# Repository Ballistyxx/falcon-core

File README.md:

# Falcon Core

<!-- <table>
  <tr>
    <td></td>
    <td></td>
  </tr>
</table> -->

A custom standalone ESP32-S3 flight controller for an indoor autonomous blimp. Successor to [Falcon Flight](https://github.com/PHS-SMCS/falcon-flight), redesigned from a Raspberry Pi Zero 2W HAT into a purpose-built 32×46mm 4-layer PCB.

Sponsored by [PCBWay](https://www.pcbway.com/).

## Specifications

- **MCU:** ESP32-S3-WROOM-1 (N8R8/N16R8) — dual-core LX7, Wi-Fi, BLE, 8MB PSRAM
- **Camera:** OV2640 via 24-pin 0.5mm FFC, 8-bit DVP interface
- **IMU:** BMI270 (6-axis accel/gyro, I2C)
- **Magnetometer:** MMC5633NJL (3-axis AMR, I2C, 1.62–3.6V)
- **ToF Sensor:** VL53L5CX (I2C)
- **Motor Drivers:** 4× DRV8212P bidirectional H-bridge
- **Battery Sensing:** Internal ADC (GPIO7)
- **Status LED:** Programmable red LED (GPIO48)
- **Board:** 32×46mm, 4-layer, matte black solder mask
- **Weight:** only 11 grams (excluding battery)

## Power

- **Battery:** BetaFPV 3.7V 300mAh 1S LiPo
- **Charging:** TP4057 via USB-C (5.1kΩ CC pull-downs)
- **Motor Power:** Direct battery feed to DRV8212P VM pins
- **Logic Isolation:** BLM18PG221SN1D ferrite bead between battery and logic rail
- **Regulators (ME6211 LDOs, SOT-23-5):**
  - 3.3V — ESP32-S3, sensors, VDDIO
  - 2.8V × 2 — OV2640 AVDD and DOVDD
  - 1.2V — OV2640 DVDD

## GPIO Assignment

| GPIO | Function |
|------|----------|
| 1, 2 | SCCB (camera I2C — SIOD, SIOC) |
| 3 | M2_IN1 |
| 4 | M3_IN2 |
| 5 | M3_IN1 |
| 6 | M1_IN2 |
| 7 | BAT_ADC (battery voltage sensing) |
| 8, 18 | Main I2C bus (SDA, SCL) |
| 9, 10, 11, 12, 13, 14, 21, 40 | OV2640 DVP data bus (D8, D7, D6, D2, D5, D3, D4, D9) |
| 15 | M4_IN1 |
| 16 | M4_IN2 |
| 17 | M2_IN2 |
| 19, 20 | USB D−/D+ |
| 38 | Camera PCLK |
| 39 | Camera XCLK |
| 41 | HREF |
| 42 | VSYNC |
| 43, 44 | UART0 debug |
| 47 | M1_IN1 |
| 48 | Red LED (1kΩ to GND) |

Camera PWDN tied to GND, RESETB tied to 3.3V.

## I2C Bus

All sensors share the main I2C bus (GPIO8/18):

- BMI270 (accel/gyro)
- MMC5633NJL (magnetometer)
- VL53L5CX (time-of-flight)

Camera SCCB runs on a separate bus (GPIO1/2).

## Motor Layout

- 2× horizontal forward-facing motors (thrust)
- 1× downward-facing altitude motor (mounted below PCB on standoff)
- 1× TBD

## Firmware

Built with ESP-IDF. Custom PID stabilization (no ArduPilot). Communicates with a laptop over WebSocket for optical flow and AprilTag detection via OpenCV.

## License

See [LICENSE](LICENSE).

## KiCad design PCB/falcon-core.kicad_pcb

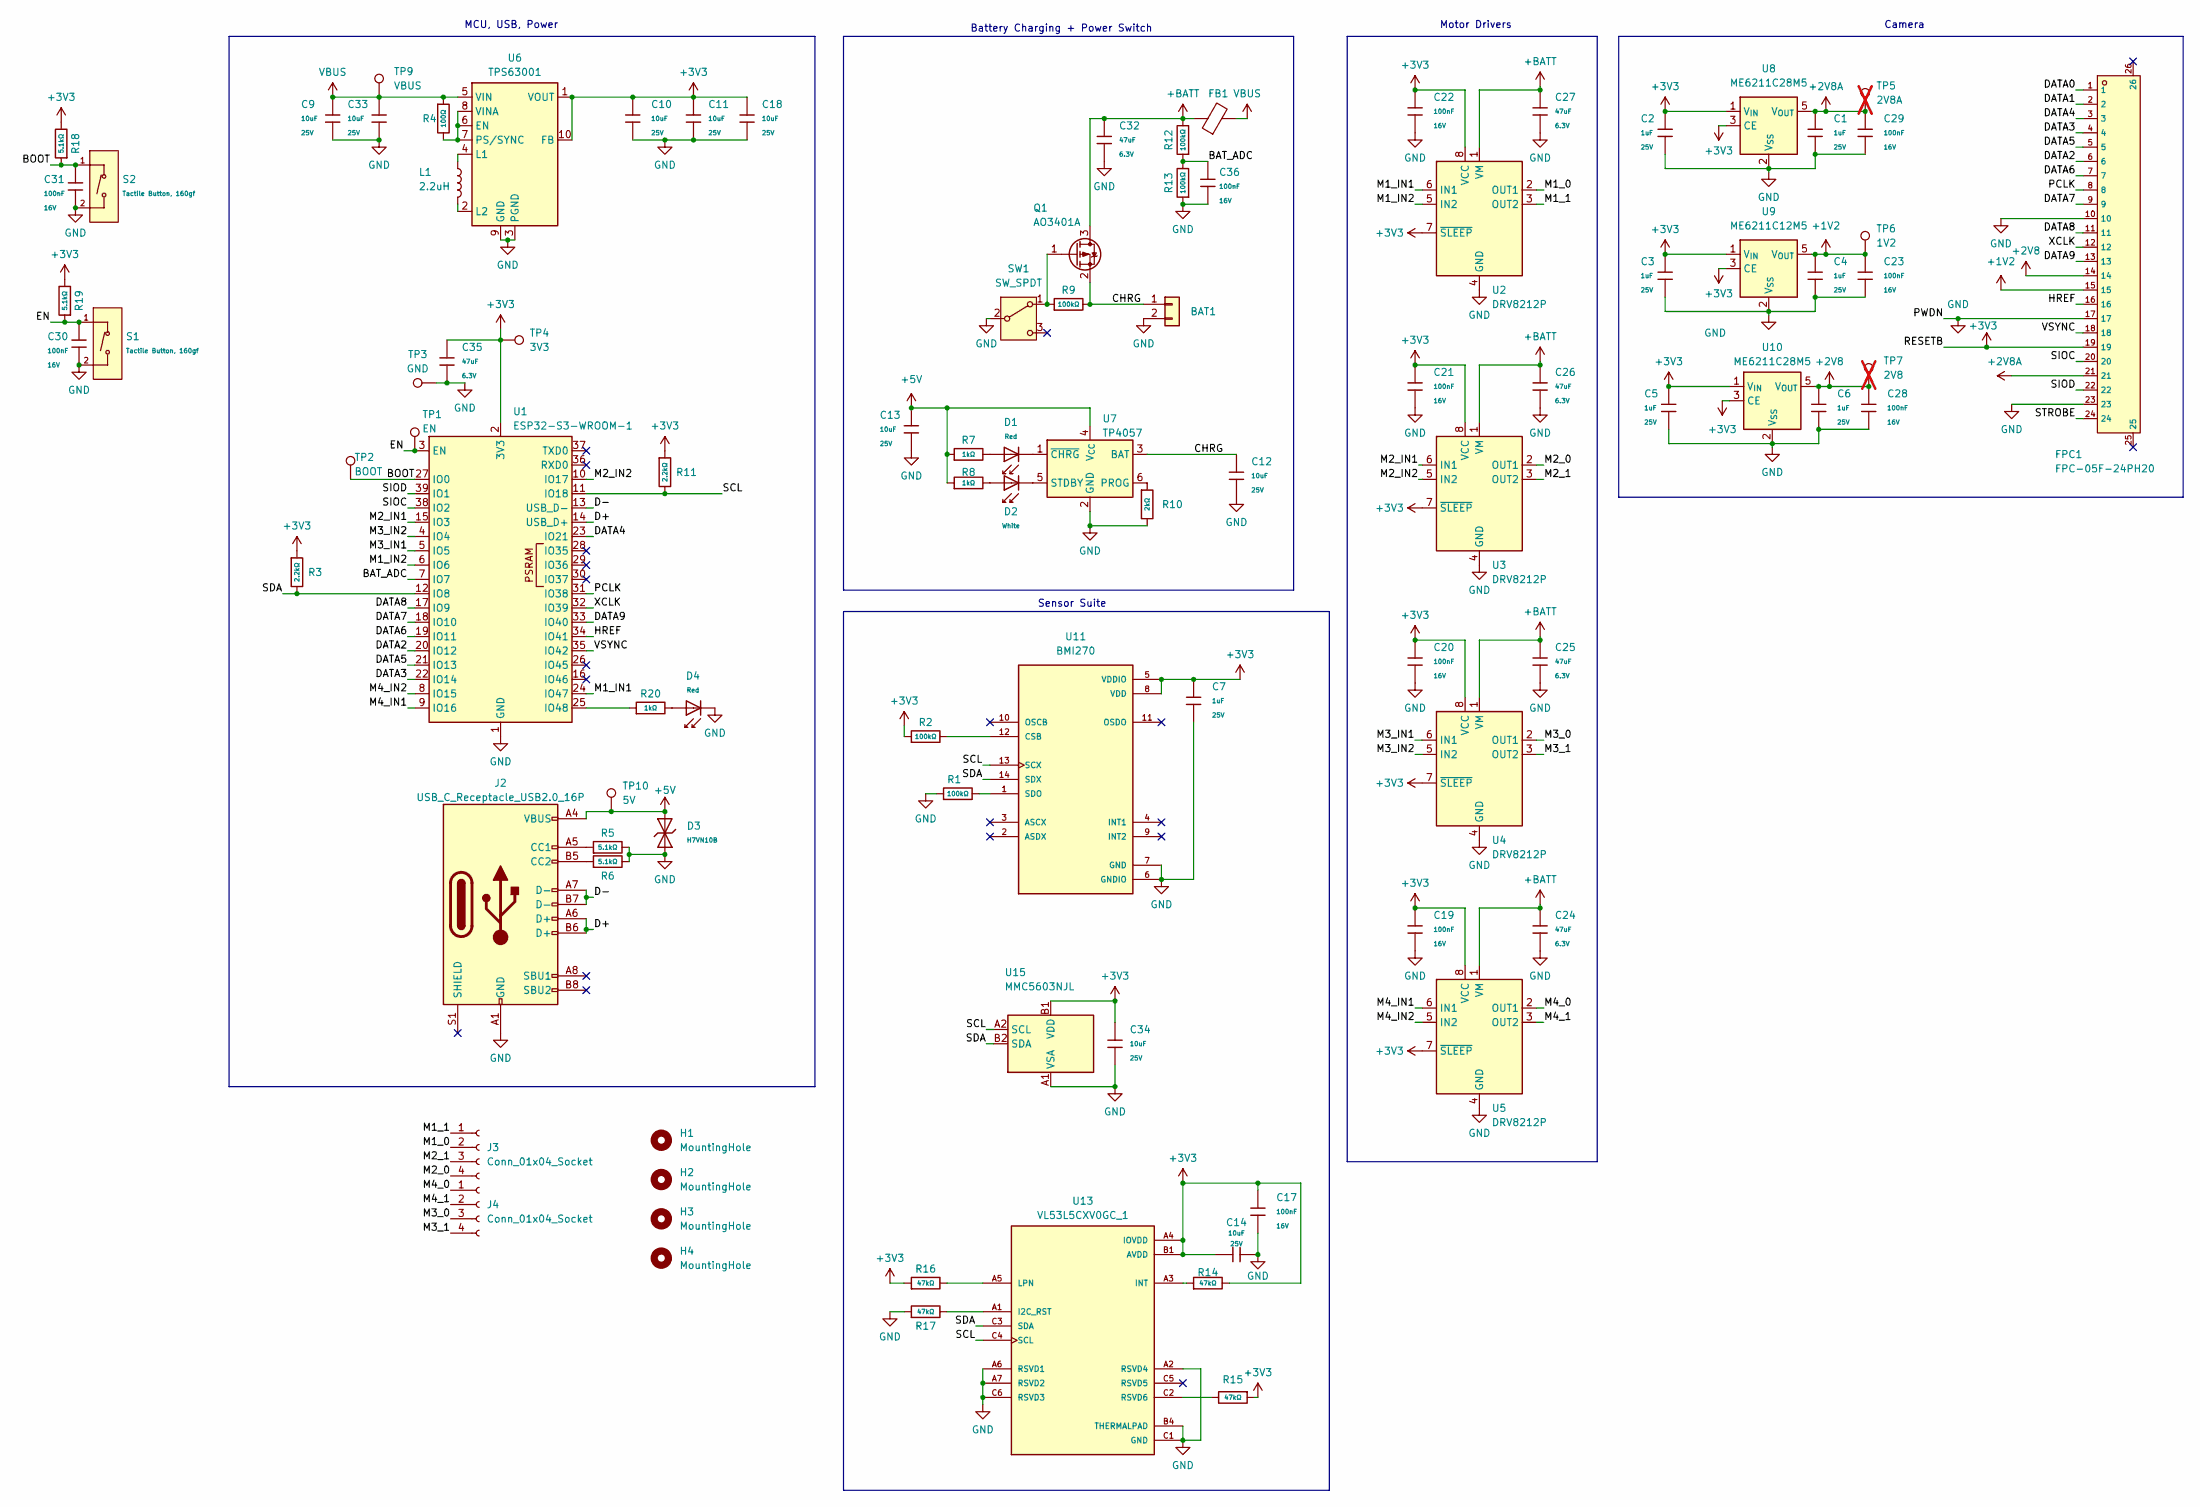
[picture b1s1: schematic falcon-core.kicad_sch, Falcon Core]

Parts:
BAT1: Conn_01x02; CONN-SMD_2P-P2.00_WF-1F200A2P; LCSC C23397052
C1, C2, C3, C4, C5, C6, C7: 1uF; C_0402; Voltage Rated 25V; Tolerance ±10%; Part CL05A105KA5NQNC; LCSC C52923
C9, C10, C11, C12, C13, C14, C18, C33, C34: 10uF; C_0603; Voltage Rated 25V; Tolerance ±20%; Part CL10A106MA8NRNC; LCSC C96446
C17, C19, C20, C21, C22, C23, C28, C29, C30, C31, C36: 100nF; C_0402; Voltage Rated 16V; Tolerance ±10%; Part CL05B104KO5NNNC; LCSC C1525
C24, C25, C26, C27, C32, C35: 47uF; C_0805; Voltage Rated 6.3V; Tolerance ±20%; Part CL21A476MQYNNNE; LCSC C16780
D1, D4: Red; D_0603; Part KT-0603R; LCSC C2286
D2: White; D_0603; Part KT-0603W; LCSC C2290
D3: H7VN10B; D_DFN1006-2L; Part H7VN10B; LCSC C20615788
FB1: FerriteBead; L_0603_1608Metric; LCSC Part Number C80165
FPC1: FPC-05F-24PH20; FPC-SMD_24P-P0.50_FPC-05F-24PH20; LCSC C2856805
H1, H2, H3, H4: MountingHole; MountingHole_3.2mm_M3_DIN965_Pad
J2: USB_C_Receptacle_USB2.0_16P; USB_C_Receptacle_GCT_USB4105-xx-A_16P_TopMnt_Horizontal; LCSC C393939
J3, J4: Conn_01x04_Socket; CONN-SMD_4P-P2.54_HX-PM2.54-1X4PWT; LCSC C46061768
L1: 2.2uH; L_APV_ANR252010; LCSC C5349606
Q1: AO3401A; SOT-23; LCSC C15127
R1, R2, R9, R12, R13: 100kΩ; R_0402; Overload Voltage (Max) 50V; Tolerance ±1%; Part 0402WGF1003TCE; LCSC C25741
R3, R11: 2.2kΩ; R_0402; Overload Voltage (Max) 50V; Tolerance ±1%; Part 0402WGF2201TCE; LCSC C25879
R4: 100Ω; R_0402; Overload Voltage (Max) 50V; Tolerance ±1%; Part 0402WGF1000TCE; LCSC C25076
R5, R6, R18, R19: 5.1kΩ; R_0402; Overload Voltage (Max) 50V; Tolerance ±1%; Part 0402WGF5101TCE; LCSC C25905
R7, R8, R20: 1kΩ; R_0402; Overload Voltage (Max) 50V; Tolerance ±1%; Part 0402WGF1001TCE; LCSC C11702
R10: 2kΩ; R_0402; Overload Voltage (Max) 50V; Tolerance ±1%; Part 0402WGF2001TCE; LCSC C4109
R14, R15, R16, R17: 47kΩ; R_0402; Overload Voltage (Max) 50V; Tolerance ±1%; Part 0402WGF4702TCE; LCSC C25792
S1, S2: Tactile Button, 160gf; SW_TS-1088-AR02016; Voltage Rating (Dc) 12V; Part TS-1088-AR02016; LCSC C720477
SW1: SW_SPDT; SW_Slide_SPDT_Angled_CK_OS102011MA1Q; LCSC C431547
TP1: EN; TestPoint_Pad_D2.0mm
TP2: BOOT; TestPoint_Pad_D2.0mm
TP3: GND; TestPoint_Pad_D2.0mm
TP4: 3V3; TestPoint_Pad_D2.0mm
TP5: 2V8A; TestPoint_Pad_D2.0mm; not fitted
TP6: 1V2; TestPoint_Pad_D2.0mm
TP7: 2V8; TestPoint_Pad_D2.0mm; not fitted
TP9: VBUS; TestPoint_Pad_D2.0mm
TP10: 5V; TestPoint_Pad_D2.0mm
U1: ESP32-S3-WROOM-1; LCSC C2913202
U2, U3, U4, U5: DRV8212P; WSON-8-1EP_2x2mm_P0.5mm_EP0.9x1.6mm_ThermalVias; LCSC C5208051
U6: TPS63001; Texas_DRC0010J_ThermalVias; LCSC C28060
U7: TP4057; TSOT-23-6; LCSC C12044
U8, U10: ME6211C28M5; SOT-23-5; LCSC C53099
U9: ME6211C12M5; SOT-23-5; LCSC C236672
U11: BMI270; XDCR_BMI270; LCSC C2836813
U13: VL53L5CXV0GC_1; XDCR_VL53L5CXV0GC_1; PARTREV 13; LCSC C3178303
U15: MMC5603NJL; WLP-4_0.86x0.86mm_P0.4mm; LCSC C404328

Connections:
+1V2: C4.1, C23.2, FPC1.15, TP6.1 (1_1), U9.5 (V_{OUT})
+2V8: C6.1, C28.2, FPC1.14, TP7.1, U10.5 (V_{OUT})
+2V8A: C1.1, C29.2, FPC1.21, TP5.1, U8.5 (V_{OUT})
+5V: C13.1, D3.2, J2.A4 (VBUS), J2.A9 (VBUS), J2.B4 (VBUS), J2.B9 (VBUS), R7.1, R8.1, TP10.1 (1_1), U7.4 (V_{CC})
+BATT: C24.1, C25.1, C26.1, C27.1, C32.1, FB1.1, Q1.3 (D), R12.2, U2.1 (VM), U3.1 (VM), U4.1 (VM), U5.1 (VM)
/BAT_ADC: C36.1, R12.1, R13.2, U1.7 (IO7)
/BOOT: C31.1, R18.1, S2.1 (A), TP2.1 (1_1), U1.27 (IO0)
/CHRG: BAT1.1, C12.1, Q1.2 (S), R9.2, U7.3 (BAT)
/D+: J2.A6 (D+), J2.B6 (D+), U1.14 (USB_D+)
/D-: J2.A7 (D-), J2.B7 (D-), U1.13 (USB_D-)
/DATA0: FPC1.1
/DATA1: FPC1.2
/DATA2: FPC1.6, U1.20 (IO12)
/DATA3: FPC1.4, U1.22 (IO14)
/DATA4: FPC1.3, U1.23 (IO21)
/DATA5: FPC1.5, U1.21 (IO13)
/DATA6: FPC1.7, U1.19 (IO11)
/DATA7: FPC1.9, U1.18 (IO10)
/DATA8: FPC1.11, U1.17 (IO9)
/DATA9: FPC1.13, U1.33 (IO40)
/HREF: FPC1.16, U1.34 (IO41)
/M1_0: J3.2, U2.2 (OUT1)
/M1_1: J3.1, U2.3 (OUT2)
/M1_IN1: U1.24 (IO47), U2.6 (IN1)
/M1_IN2: U1.6 (IO6), U2.5 (IN2)
/M2_0: J3.4, U3.2 (OUT1)
/M2_1: J3.3, U3.3 (OUT2)
/M2_IN1: U1.15 (IO3), U3.6 (IN1)
/M2_IN2: U1.10 (IO17), U3.5 (IN2)
/M3_0: J4.3, U4.2 (OUT1)
/M3_1: J4.4, U4.3 (OUT2)
/M3_IN1: U1.5 (IO5), U4.6 (IN1)
/M3_IN2: U1.4 (IO4), U4.5 (IN2)
/M4_0: J4.1, U5.2 (OUT1)
/M4_1: J4.2, U5.3 (OUT2)
/M4_IN1: U1.9 (IO16), U5.6 (IN1)
/M4_IN2: U1.8 (IO15), U5.5 (IN2)
/PCLK: FPC1.8, U1.31 (IO38)
/SCL: R11.2, U1.11 (IO18), U11.13 (SCX), U13.C4 (SCL), U15.A2 (SCL)
/SDA: R3.2, U1.12 (IO8), U11.14 (SDX), U13.C3 (SDA), U15.B2 (SDA)
/SIOC: FPC1.20, U1.38 (IO2)
/SIOD: FPC1.22, U1.39 (IO1)
/STROBE: FPC1.24
/VSYNC: FPC1.18, U1.35 (IO42)
/XCLK: FPC1.12, U1.32 (IO39)
GND: BAT1.2, C1.2, C2.2, C3.2, C4.2, C5.2, C6.2, C7.2, C9.2, C10.2, C11.2, C12.2, C13.2, C14.2, C17.2, C18.2, C19.1, C20.1, C21.1, C22.1, C23.1, C24.2, C25.2, C26.2, C27.2, C28.1, C29.1, C30.2, C31.2, C32.2, C33.2, C34.1, C35.2, C36.2, D3.1, D4.1, FPC1.10, FPC1.17, FPC1.23, J2.A1 (GND), J2.A12 (GND), J2.B1 (GND), J2.B12 (GND), R1.1, R5.2, R6.2, R10.2, R13.1, R17.1, S1.2 (B), S2.2 (B), SW1.2 (B), TP3.1 (1_1), U1.1 (GND), U1.40 (GND), U1.41 (GND), U2.4 (GND), U2.9 (GND), U3.4 (GND), U3.9 (GND), U4.4 (GND), U4.9 (GND), U5.4 (GND), U5.9 (GND), U6.3 (PGND), U6.9 (GND), U6.11 (PGND), U7.2 (GND), U8.2 (V_{SS}), U9.2 (V_{SS}), U10.2 (V_{SS}), U11.6 (GNDIO), U11.7 (GND), U13.A2 (RSVD4), U13.A6 (RSVD1), U13.A7 (RSVD2), U13.B4 (THERMALPAD), U13.C1 (GND), U13.C6 (RSVD3), U13.C7 (GND), U15.A1 (VSA); also elsewhere on the board
unnamed: D1.2, R7.2
unnamed: D2.2, R8.2
unnamed: D4.2, R20.2
unnamed: J2.A5 (CC1), R5.1
unnamed: J2.B5 (CC2), R6.1
unnamed: Q1.1 (G), R9.1, SW1.1 (A)
unnamed: R20.1, U1.25 (IO48)
unnamed: R4.2, U6.6 (EN), U6.7 (PS/SYNC), U6.8 (VINA)
unnamed: L1.1, U6.4 (L1)
unnamed: L1.2, U6.2 (L2)
unnamed: R10.1, U7.6 (PROG)
unnamed: D2.1, U7.5 (STDBY)
unnamed: D1.1, U7.1 (~CHRG)
unnamed: R2.2, U11.12 (CSB)
unnamed: R1.2, U11.1 (SDO)
unnamed: R17.2, U13.A1 (I2C_RST)
unnamed: R14.1, U13.A3 (INT)
unnamed: R16.2, U13.A5 (LPN)
unnamed: R15.2, U13.C2 (RSVD6)
VBUS: C9.1, C33.1, FB1.2, R4.1, TP9.1 (1_1), U6.5 (VIN)

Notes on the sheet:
Battery Charging + Power Switch
Sensor Suite
MCU, USB, Power
Camera
Motor Drivers

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
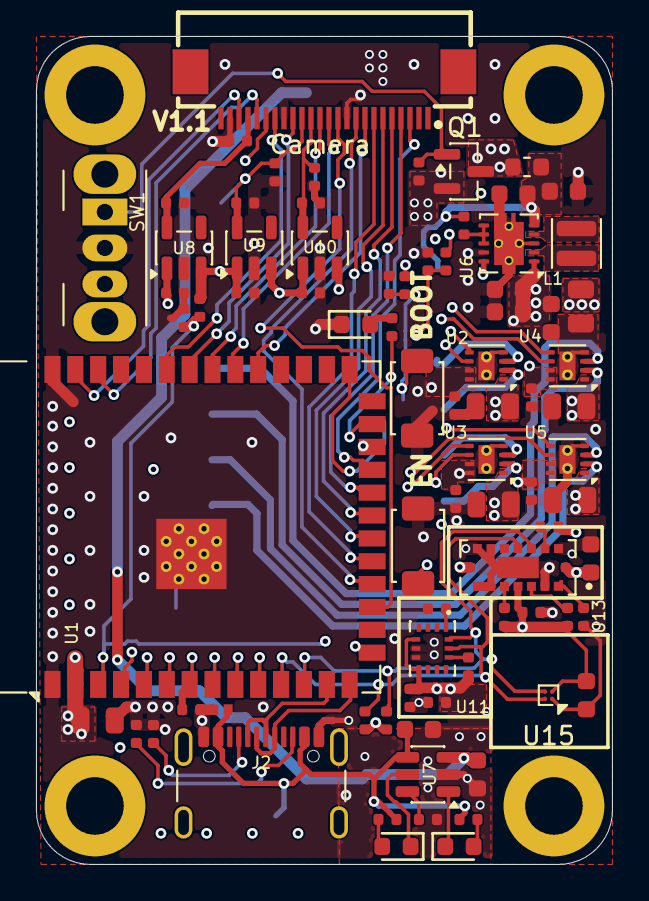
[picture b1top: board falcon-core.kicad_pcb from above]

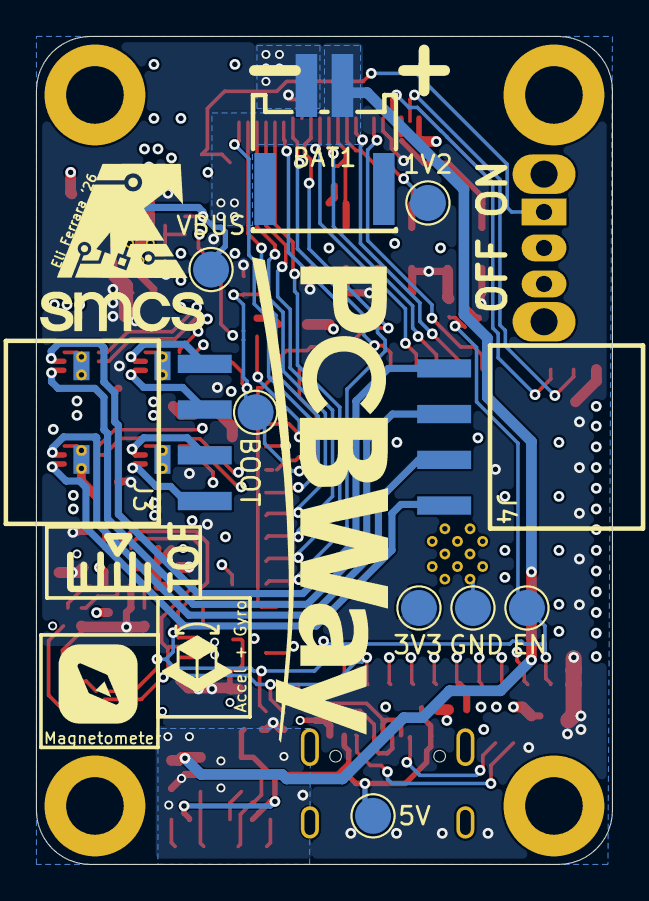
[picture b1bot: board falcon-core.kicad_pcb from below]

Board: 4 copper layers, 32.0 x 46.0 mm, 93 parts (10 on the bottom side), 65 nets.

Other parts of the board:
C30#2: 100nF; C_0402

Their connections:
GND: C30#2.2; also elsewhere on the board

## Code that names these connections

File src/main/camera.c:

#include "camera.h"
#include "esp_camera.h"
#include "esp_log.h"

static const char *TAG = "camera";
static bool s_ok;

/* DVP pin mapping from the confirmed Falcon Core pinout.
 * esp_camera pin_d0..d7 correspond to OV2640 data lines D2..D9. */
#define CAM_PIN_PWDN    -1    /* tied low in hardware  */
#define CAM_PIN_RESET   -1    /* tied high in hardware */
#define CAM_PIN_XCLK    39
#define CAM_PIN_SIOD    1     /* SCCB SDA */
#define CAM_PIN_SIOC    2     /* SCCB SCL */
#define CAM_PIN_D7      40    /* D9 */
#define CAM_PIN_D6      9     /* D8 */
#define CAM_PIN_D5      10    /* D7 */
#define CAM_PIN_D4      11    /* D6 */
#define CAM_PIN_D3      13    /* D5 */
#define CAM_PIN_D2      21    /* D4 */
#define CAM_PIN_D1      14    /* D3 */
#define CAM_PIN_D0      12    /* D2 */
#define CAM_PIN_VSYNC   42
#define CAM_PIN_HREF    41
#define CAM_PIN_PCLK    38

esp_err_t camera_init(void)
{
    camera_config_t config = {
        .pin_pwdn = CAM_PIN_PWDN,
        .pin_reset = CAM_PIN_RESET,
        .pin_xclk = CAM_PIN_XCLK,
        .pin_sccb_sda = CAM_PIN_SIOD,
        .pin_sccb_scl = CAM_PIN_SIOC,
        .pin_d7 = CAM_PIN_D7,
        .pin_d6 = CAM_PIN_D6,
        .pin_d5 = CAM_PIN_D5,
        .pin_d4 = CAM_PIN_D4,
        .pin_d3 = CAM_PIN_D3,
        .pin_d2 = CAM_PIN_D2,
        .pin_d1 = CAM_PIN_D1,
        .pin_d0 = CAM_PIN_D0,
        .pin_vsync = CAM_PIN_VSYNC,
        .pin_href = CAM_PIN_HREF,
        .pin_pclk = CAM_PIN_PCLK,

        .xclk_freq_hz = 20000000,
        /* On the ESP32-S3 the camera XCLK is generated by LEDC; keep it off
         * LEDC timer 0 / channels 0-5 used by the motor PWM. */
        .ledc_timer = LEDC_TIMER_1,
        .ledc_channel = LEDC_CHANNEL_6,

        .pixel_format = PIXFORMAT_JPEG,
        .frame_size = FRAMESIZE_VGA,     /* 640x480, 4:3 */
        .jpeg_quality = 12,              /* 0-63, lower = higher quality */
        .fb_count = 2,
        .fb_location = CAMERA_FB_IN_PSRAM,
        .grab_mode = CAMERA_GRAB_WHEN_EMPTY,
    };

    esp_err_t err = esp_camera_init(&config);
    if (err != ESP_OK) {
        ESP_LOGE(TAG, "esp_camera_init failed: 0x%x", err);
        s_ok = false;
        return err;
    }

    sensor_t *s = esp_camera_sensor_get();
    if (s) {
        s->set_vflip(s, 0);
        s->set_hmirror(s, 0);
    }
    s_ok = true;
    ESP_LOGI(TAG, "OV2640 ready (VGA JPEG)");
    return ESP_OK;
}

bool camera_ok(void)
{
    return s_ok;
}

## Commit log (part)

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2026-05-12 add hardware design + preliminary readme
